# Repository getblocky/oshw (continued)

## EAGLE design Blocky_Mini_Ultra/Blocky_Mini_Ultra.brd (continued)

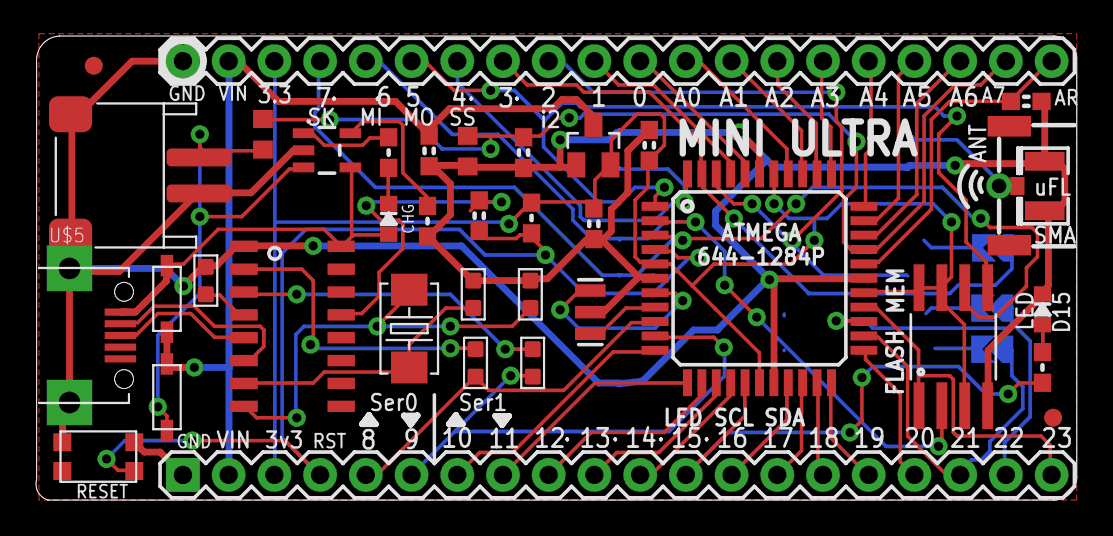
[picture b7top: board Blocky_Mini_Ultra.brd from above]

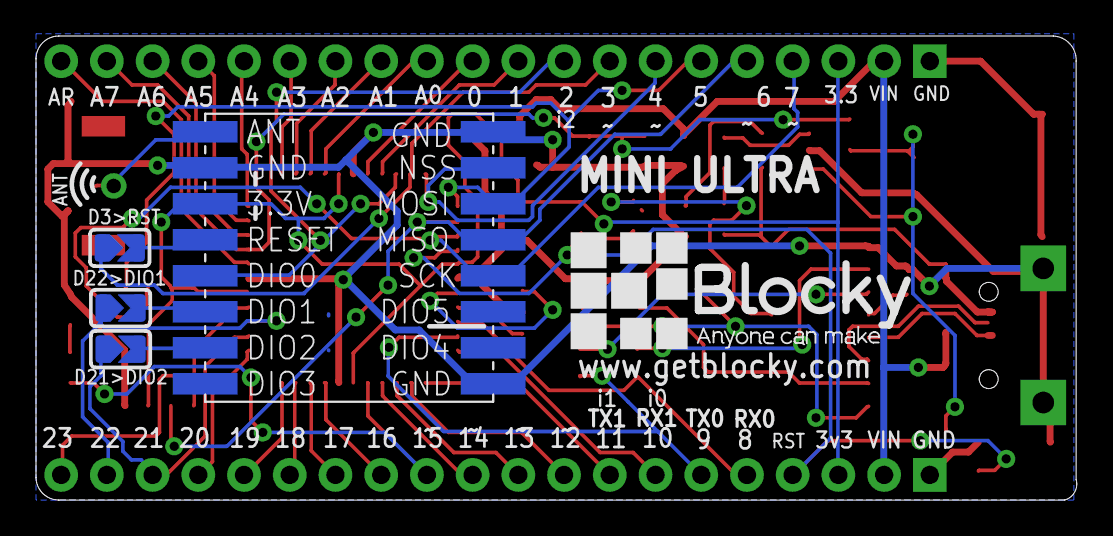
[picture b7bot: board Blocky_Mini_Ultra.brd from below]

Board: 2 copper layers, 57.8 x 25.8 mm, 42 parts (5 on the bottom side), 57 nets.

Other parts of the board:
U$3: BLOCKY_LOGO

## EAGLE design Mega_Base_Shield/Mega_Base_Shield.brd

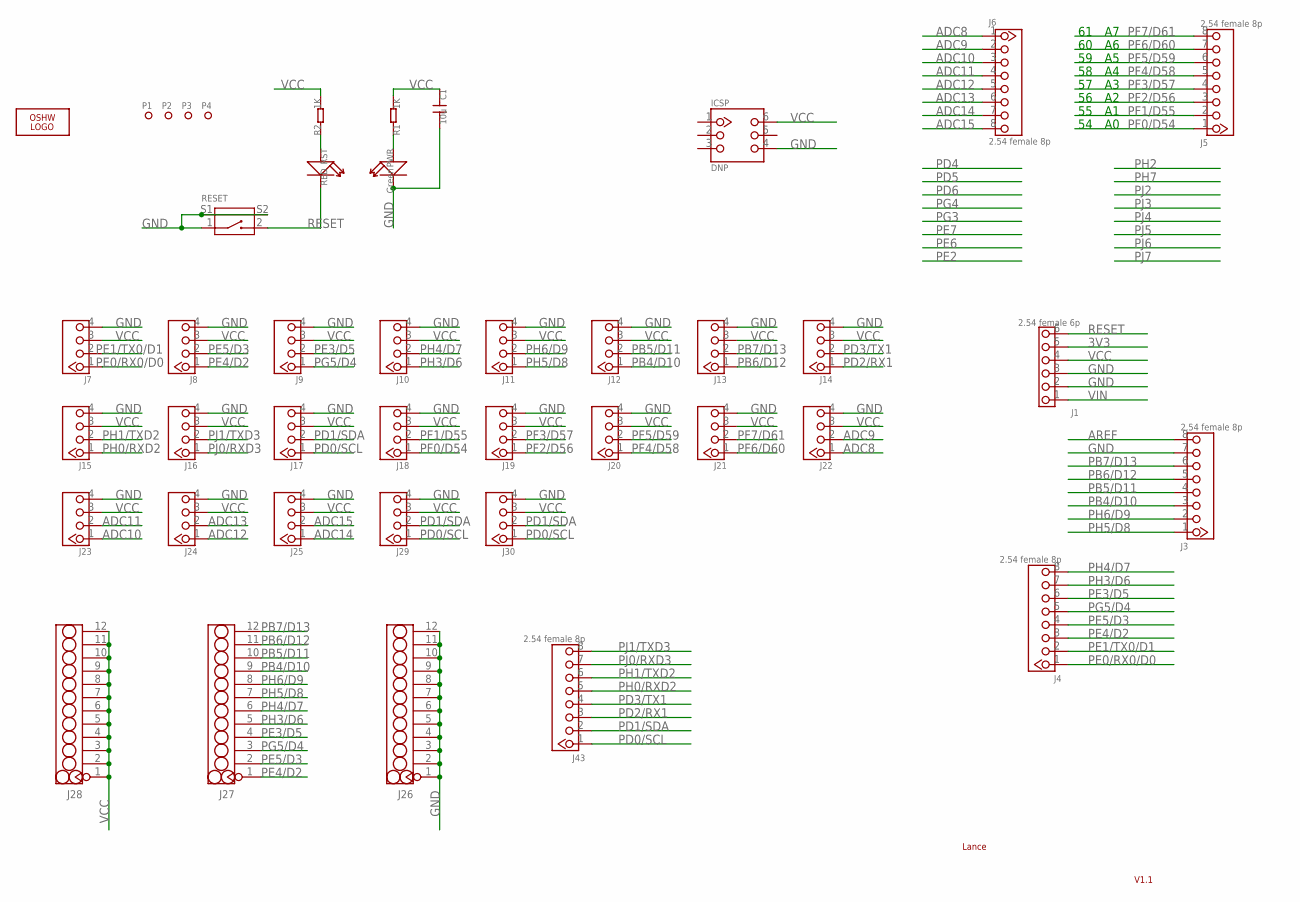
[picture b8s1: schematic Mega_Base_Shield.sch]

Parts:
C1: 10u; 0805
ICSP: DNP; 2X3P-2.54-LEADED-60/35
J1: 2.54 female 6p; 6P-2.54-LEADED
J3, J4, J5, J6, J43: 2.54 female 8p; 8P-2.54-LEADED
J7, J14, J15, J16, J17: TWIG-2.0-LEADED'90D'; 4P-LEADED-2.0-90
J8, J9, J10, J11, J12, J13, J18, J19, J20, J21, J22, J23, J24, J25, J29, J30: TWIG-2.0-LEADED; 4P-LEADED-2.0
J26, J27, J28: HEADER-12P-2.54; 12P-2.54-LEADED
LOGO1: LOGO-OSHW-FILLX0200-NT; OSHW_FILLX200_NOTEXT
P1, P2, P3, P4: PAD-MARK'ANNULAR'; ROUND-MARK-1.0
PWR: Green; D0603
R1, R2: 1K; 0402
RESET: BUTTON-2+2P'TS-1188E'; 4P-SMD-L7.0*W3.5*H3.5MM-90D
RST: RED; D0603

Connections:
3V3: J1.5
ADC8: J6.1, J22.1
ADC9: J6.2, J22.2
ADC10: J6.3, J23.1
ADC11: J6.4, J23.2
ADC12: J6.5, J24.1
ADC13: J6.6, J24.2
ADC14: J6.7, J25.1
ADC15: J6.8, J25.2
AREF: J3.8
GND: C1.2, ICSP.4, J1.2, J1.3, J3.7, J7.4, J8.4, J9.4, J10.4, J11.4, J12.4, J13.4, J14.4, J15.4, J16.4, J17.4, J18.4, J19.4, J20.4, J21.4, J22.4, J23.4, J24.4, J25.4, J26.1, J26.2, J26.3, J26.4, J26.5, J26.6, J26.7, J26.8, J26.9, J26.10, J26.11, J26.12, J29.4, J30.4, PWR.-, RESET.1, RESET.S1, RESET.S2
unnamed: PWR.+, R1.1
unnamed: R2.1, RST.+
PB4/D10: J3.3, J12.1, J27.9
PB5/D11: J3.4, J12.2, J27.10
PB6/D12: J3.5, J13.1, J27.11
PB7/D13: J3.6, J13.2, J27.12
PD0/SCL: J17.1, J29.1, J30.1, J43.1
PD1/SDA: J17.2, J29.2, J30.2, J43.2
PD2/RX1: J14.1, J43.3
PD3/TX1: J14.2, J43.4
PE0/RX0/D0: J4.1, J7.1
PE1/TX0/D1: J4.2, J7.2
PE3/D5: J4.6, J9.2, J27.4
PE4/D2: J4.3, J8.1, J27.1
PE5/D3: J4.4, J8.2, J27.2
PF0/D54: J5.1, J18.1
PF1/D55: J5.2, J18.2
PF2/D56: J5.3, J19.1
PF3/D57: J5.4, J19.2
PF4/D58: J5.5, J20.1
PF5/D59: J5.6, J20.2
PF6/D60: J5.7, J21.1
PF7/D61: J5.8, J21.2
PG5/D4: J4.5, J9.1, J27.3
PH0/RXD2: J15.1, J43.5
PH1/TXD2: J15.2, J43.6
PH3/D6: J4.7, J10.1, J27.5
PH4/D7: J4.8, J10.2, J27.6
PH5/D8: J3.1, J11.1, J27.7
PH6/D9: J3.2, J11.2, J27.8
PJ0/RXD3: J16.1, J43.7
PJ1/TXD3: J16.2, J43.8
RESET: J1.6, RESET.2, RST.-
VCC: C1.1, ICSP.6, J1.4, J7.3, J8.3, J9.3, J10.3, J11.3, J12.3, J13.3, J14.3, J15.3, J16.3, J17.3, J18.3, J19.3, J20.3, J21.3, J22.3, J23.3, J24.3, J25.3, J28.1, J28.2, J28.3, J28.4, J28.5, J28.6, J28.7, J28.8, J28.9, J28.10, J28.11, J28.12, J29.3, J30.3, R1.2, R2.2
VIN: J1.1

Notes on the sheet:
Lance
V1.1

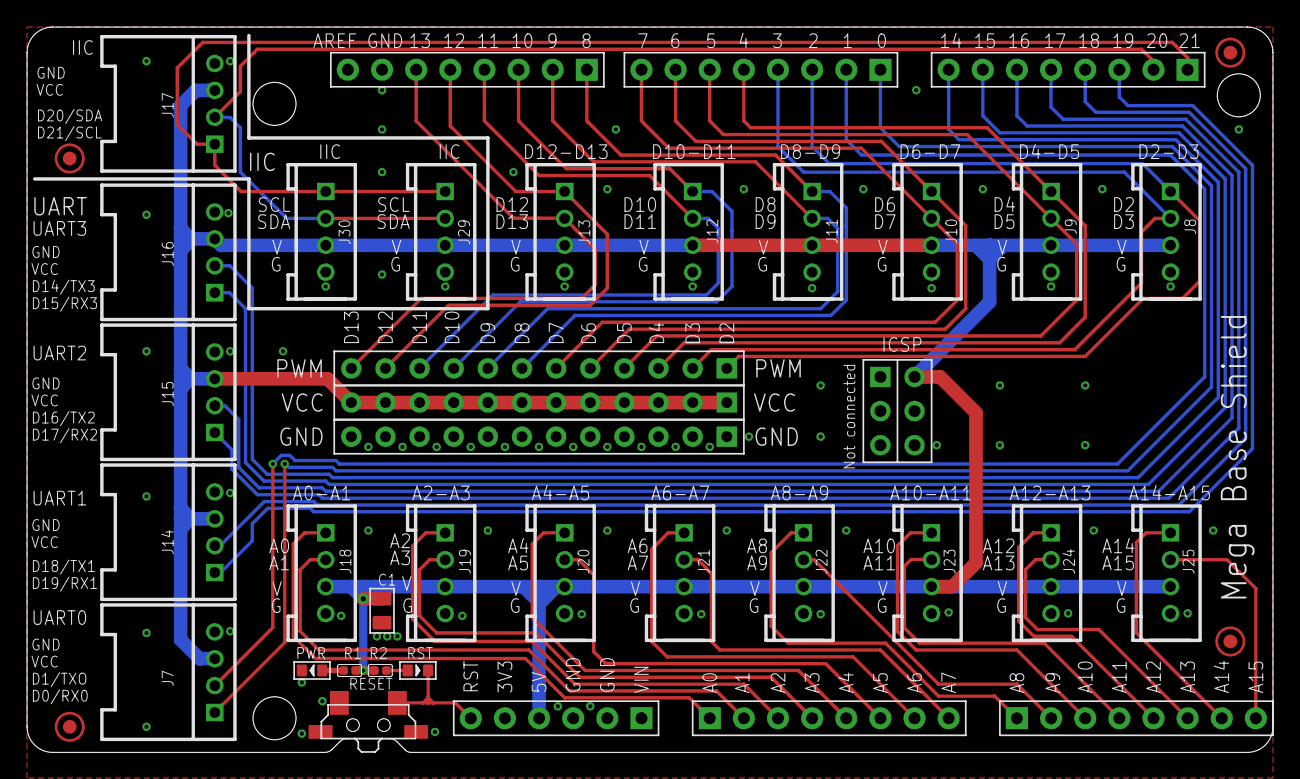
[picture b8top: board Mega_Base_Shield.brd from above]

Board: 2 copper layers, 92.7 x 54.0 mm, 42 parts (1 on the bottom side), 43 nets.

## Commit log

2018-09-24 Test commit
2018-09-25 Add design for Blocky Uno and BOM
2018-09-27 Add shield for STM32 Blue Pill
2018-09-28 Update Blue Pill Shield to add UART header
2018-09-29 Add Mini Ultra
2018-09-29 Update schematic
2018-09-30 Add Base Shield for Mini Ultra
2018-09-30 Update gerber and add exported images for Mini Ultra
2018-10-01 Add Arduino Mini
2018-10-02 Finish Arduino Mini
2018-10-02 Replace usb for mini ultra
2018-10-02 Correct silk for Arduino Mini
2018-10-03 Update Uno Lora Shield
2018-10-03 Add Lora shield for Rasp Pi
2018-10-03 Add NodeMCU Base Shield
2018-10-03 Add base shield for esp32
2018-10-03 Add base shield for Uno
2018-10-03 Update Blocky Uno
2018-10-03 Add Lora shield for Lolin32 Lite
2018-10-03 Add shield for Mega
2018-10-04 Correct error for Ultra Mini
2018-10-04 Add Blocky Wifi
2018-10-05 Add Blocky NODE
2018-10-05 Update Blocky NODE images
2018-10-15 Add STM Zero board
2018-11-03 Update Blocky Node
2018-11-03 Update silk for Blocky Node
2018-12-13 Update schematic for mini ultra
2018-12-21 Add Blocky Uno ESP32
2019-01-02 Fix error with GND trace
2019-01-03 Update Uno to ver 2 to use atmega328p-au and CH340C
2019-01-03 Change name Blocky ESP32
2019-01-03 Update frame info
2019-01-05 Add board Blocky STM32F103
2019-02-12 Add v1.1 for ESP32 UNO
2019-02-12 Rearrange folder for v1.0
2019-02-13 Correct silk for Uno
2019-02-13 Rearrange file for Uno
2019-02-22 Update pinout for Uno ESP32
2019-03-28 Add new product line: BlockyBit
2019-04-02 Update new layout for blockybit
